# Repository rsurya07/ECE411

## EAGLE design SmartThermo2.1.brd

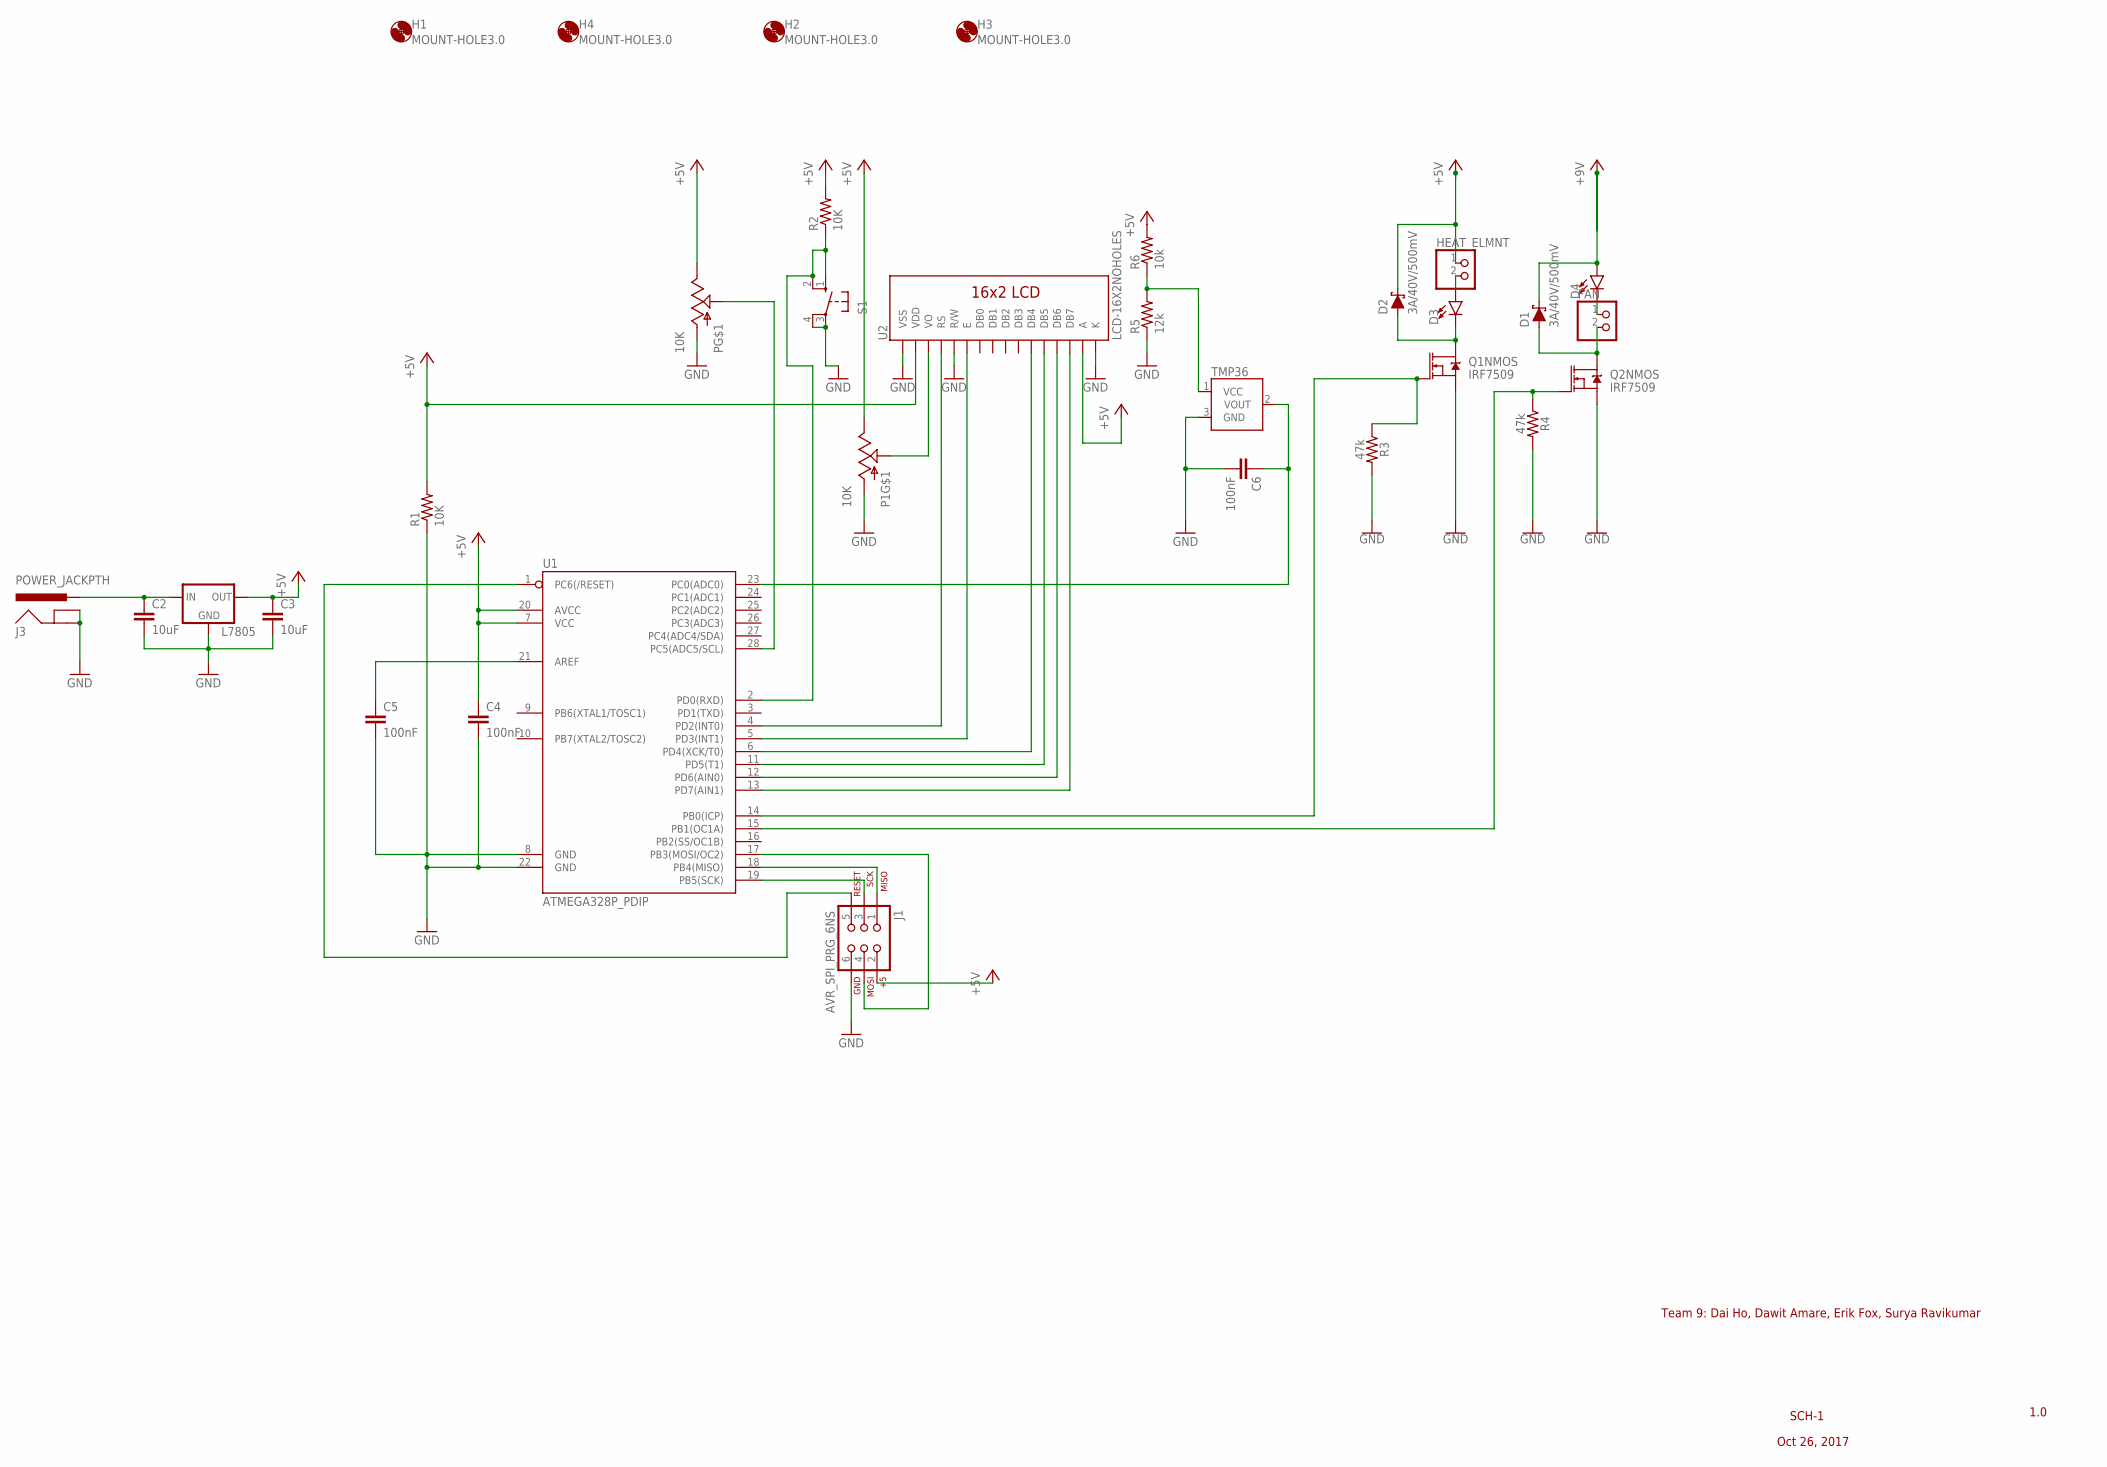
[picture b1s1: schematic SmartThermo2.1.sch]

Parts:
C2, C3: 10uF; C7.5B3
C4, C5, C6: 100nF; C2.5-2
D1, D2: 3A/40V/500mV; SMA-DIODE
D3, D4: LED3MM; LED_3MM
FAN: PINHD-1X2/90; 1X02/90
H1, H2, H3, H4: MOUNT-HOLE3.0; 3,0
HEAT_ELMNT: PINHD-1X2/90; 1X02/90
J1: AVR_SPI_PRG_6NS; 2X3-NS
J3: POWER_JACKPTH; POWER_JACK_PTH
L7805: 78XXL
P, P1: 10K; POT_PTH
Q1, Q2: IRF7509; MSOP8
R1, R2: 10K; 1206
R3, R4: 47k; 0603
R5: 12k; 0204/5
R6: 10k; 0204/5
S1: 10-XX; B3F-10XX
TMP36: TMP36GT9; TO-92
U1: ATMEGA328P_PDIP; DIL28-3
U2: LCD-16X2NOHOLES; LCD-16X2_NOHOLES

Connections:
+5V: C3.1, C4.1, D1.C, D2.C, D4.A, HEAT_ELMNT.1, J1.2, L7805.OUT, P.E@2 (E), P1.E@2 (E), R1.2, R2.2, R6.2, U1.7 (VCC), U1.20 (AVCC), U2.2 (VDD), U2.15 (A)
GND: C2.2, C3.2, C4.2, C5.2, C6.2, J1.6, J3.GND, J3.GNDBREAK, L7805.GND, P.E@1 (A), P1.E@1 (A), Q1.1 (S), Q2.1 (S), R1.1, R3.2, R4.2, R5.1, S1.3, S1.4 (P1), TMP36.3 (GND), U1.8 (GND), U1.22 (GND), U2.1 (VSS), U2.5 (R/W), U2.16 (K)
unnamed: C6.1, TMP36.2 (VOUT), U1.23 (PC0(ADC0))
unnamed: P.WAND (S), U1.28 (PC5(ADC5/SCL))
unnamed: Q2.2 (G), R4.1, U1.15 (PB1(OC1A))
unnamed: U1.4 (PD2(INT0)), U2.4 (RS)
unnamed: P1.WAND (S), U2.3 (VO)
unnamed: U1.5 (PD3(INT1)), U2.6 (E)
unnamed: U1.6 (PD4(XCK/T0)), U2.11 (DB4)
unnamed: U1.11 (PD5(T1)), U2.12 (DB5)
unnamed: U1.12 (PD6(AIN0)), U2.13 (DB6)
unnamed: U1.13 (PD7(AIN1)), U2.14 (DB7)
unnamed: C2.1, J3.PWR, L7805.IN
unnamed: D1.A, FAN.2, Q2.7 (D), Q2.8 (D)
unnamed: R5.2, R6.1, TMP36.1 (VCC)
unnamed: R2.1, S1.1 (S), S1.2 (S1), U1.2 (PD0(RXD))
unnamed: J1.1, U1.18 (PB4(MISO))
unnamed: D3.A, HEAT_ELMNT.2
unnamed: J1.4, U1.17 (PB3(MOSI/OC2))
unnamed: Q1.2 (G), R3.1, U1.14 (PB0(ICP))
unnamed: J1.3, U1.19 (PB5(SCK))
unnamed: D2.A, D3.K (C), Q1.7 (D), Q1.8 (D)
unnamed: D4.K (C), FAN.1
unnamed: C5.1, U1.21 (AREF)
unnamed: J1.5, U1.1 (PC6(/RESET))

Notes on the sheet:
Team 9: Dai Ho, Dawit Amare, Erik Fox, Surya Ravikumar
1.0
SCH-1
Oct 26, 2017

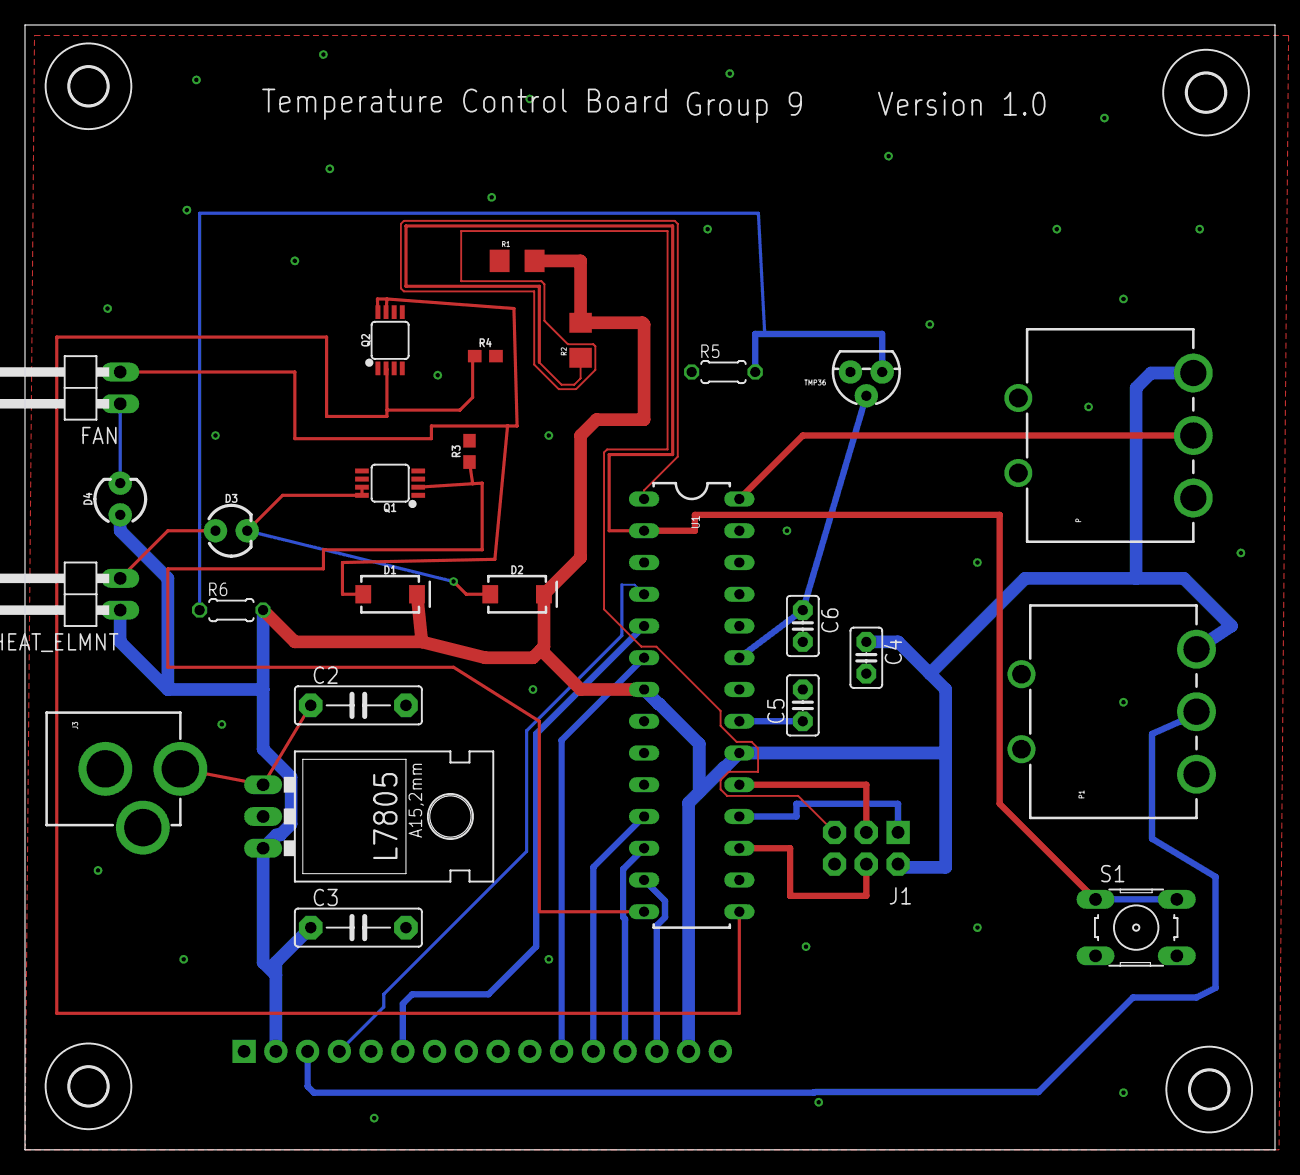
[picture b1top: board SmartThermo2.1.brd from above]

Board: 2 copper layers, 100.0 x 90.0 mm, 32 parts (0 on the bottom side), 25 nets.

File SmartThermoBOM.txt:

Partlist exported from /Users/erikfox/Downloads/ECE411---Group-9-master/SmartThermo1.9.sch at 11/20/17 6:06 PM

Part       Value           Device               Package          Description                                MF MPN      OC_FARNELL OC_NEWARK PROD_ID     VALUE       
C2         10uF            C7.5/3               C7.5B3           CAPACITOR                                                                                           
C3         10uF            C7.5/3               C7.5B3           CAPACITOR                                                                                           
C4         100nF           C2.5/2               C2.5-2           CAPACITOR                                                                                           
C5         100nF           C2.5/2               C2.5-2           CAPACITOR                                                                                           
C6         100nF           C2.5/2               C2.5-2           CAPACITOR                                                                                           
D1         3A/40V/500mV    DIODE-SCHOTTKY-B340A SMA-DIODE        Schottky diode                                                              DIO-09886   3A/40V/500mV
D2         3A/40V/500mV    DIODE-SCHOTTKY-B340A SMA-DIODE        Schottky diode                                                              DIO-09886   3A/40V/500mV
D3                         LED3MM               LED_3MM          LED (Generic)                                                               DIO-08794               
D4                         LED3MM               LED_3MM          LED (Generic)                                                               DIO-08794               
FAN                        PINHD-1X2/90         1X02/90          PIN HEADER                                                                                          
H1         MOUNT-HOLE3.0   MOUNT-HOLE3.0        3,0              MOUNTING HOLE with drill center marker                                                              
H2         MOUNT-HOLE3.0   MOUNT-HOLE3.0        3,0              MOUNTING HOLE with drill center marker                                                              
H3         MOUNT-HOLE3.0   MOUNT-HOLE3.0        3,0              MOUNTING HOLE with drill center marker                                                              
H4         MOUNT-HOLE3.0   MOUNT-HOLE3.0        3,0              MOUNTING HOLE with drill center marker                                                              
HEAT_ELMNT                 PINHD-1X2/90         1X02/90          PIN HEADER                                                                                          
J1         AVR_SPI_PRG_6NS AVR_SPI_PRG_6NS      2X3-NS           AVR ISP 6 Pin                                                                                       
J3         POWER_JACKPTH   POWER_JACKPTH        POWER_JACK_PTH   Power Jack                                                                  CONN-08197              
L7805                      78XXL                78XXL            VOLTAGE REGULATOR                                                                                   
P          10K             POT_SWITCHPOT_PTH    POT_PTH          Potentiometer w/ switch.                                                                            
P1         10K             POT_SWITCHPOT_PTH    POT_PTH          Potentiometer w/ switch.                                                                            
Q1         IRF7509         IRF7509              MSOP8            Dual N and P Channel MOSFET                                                 TRANS-07913             
Q2         IRF7509         IRF7509              MSOP8            Dual N and P Channel MOSFET                                                 TRANS-07913             
R1         10K             RESISTOR1206         1206             Resistor                                                                                            
R2         10K             RESISTOR1206         1206             Resistor                                                                                            
R3         47k             47KOHM-0603-1/10W-1% 0603             47kΩ resistor                                                               RES-07871   47k         
R4         47k             47KOHM-0603-1/10W-1% 0603             47kΩ resistor                                                               RES-07871   47k         
R5         12k             R-US_0204/5          0204/5           RESISTOR, American symbol                                                                           
R6         10k             R-US_0204/5          0204/5           RESISTOR, American symbol                                                                           
S1                         10-XX                B3F-10XX         OMRON SWITCH                                  B3F-1000 176432     36M3542                           
TMP36                      TMP36GT9             TO-92            Precision degC temp sensor, analog out                                                              
U1         ATMEGA328P_PDIP ATMEGA328P_PDIP      DIL28-3          uC used in the Arduino                                                                              
U2         LCD-16X2NOHOLES LCD-16X2NOHOLES      LCD-16X2_NOHOLES Standard text-only 16x2 parallel input LCD

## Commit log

2017-10-06 Create Ideas
2017-10-06 Update Ideas
2017-10-08 Create Pick 4 fav
2017-10-08 Update Pick 4 fav
2017-10-10 Create Project Proposal
2017-10-12 Create TA and Professor
2017-10-12 Create Part Idea
2017-10-12 Update Part Idea
2017-11-18 Create Button-Toggle-AUTO-ON_OFF.c
    This toggles Auto on or off. On Auto off, Potentiometer needs to be activated and LCD should display value. Once value sets, use it to adjust temperature.
2017-11-23 Create lcd _and_sensor
2017-11-29 Update this file
    Code including all parts: LCD, Heating, Cooling, and LEDs. update this code moving forward
2017-12-07 Create HIgh Level Algorithm
2017-12-07 Create LICENSE

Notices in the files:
parts and their libraries:
SparkFun-DiscreteSemi: Licensing: Creative Commons ShareAlike 4.0 International - https://creativecommons.org/licenses/by-sa/4.0
